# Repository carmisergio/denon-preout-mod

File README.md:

# Denon AVR-X1300W Pre-out mod

The scope of this project is adding line-level outputs to the Denon AVR-X1300W AV Receiver.
This can be acheived by getting the low-level signals from the digital board of the receiver before they make their way to the power amp board.

The "Vampire PCB" is soldered directly to the digital board of the receiverr, and provides an 8-pin JST PH connector with the signals. A small length of shielded cable brings them to the back panel of the unit, where removing the AM/FM tuner unit provides a convenient place to mount a miniature circular connector.

An external "Gain Box" amplifies the ~150Vrms internal signal to a usable (variable) line level with a single stage of op-amp amplification. It also processes the 12V signal coming from the receiver to operate muting relays on the output and generate a standard 12V trigger signal which can be used to control the amplifiers.

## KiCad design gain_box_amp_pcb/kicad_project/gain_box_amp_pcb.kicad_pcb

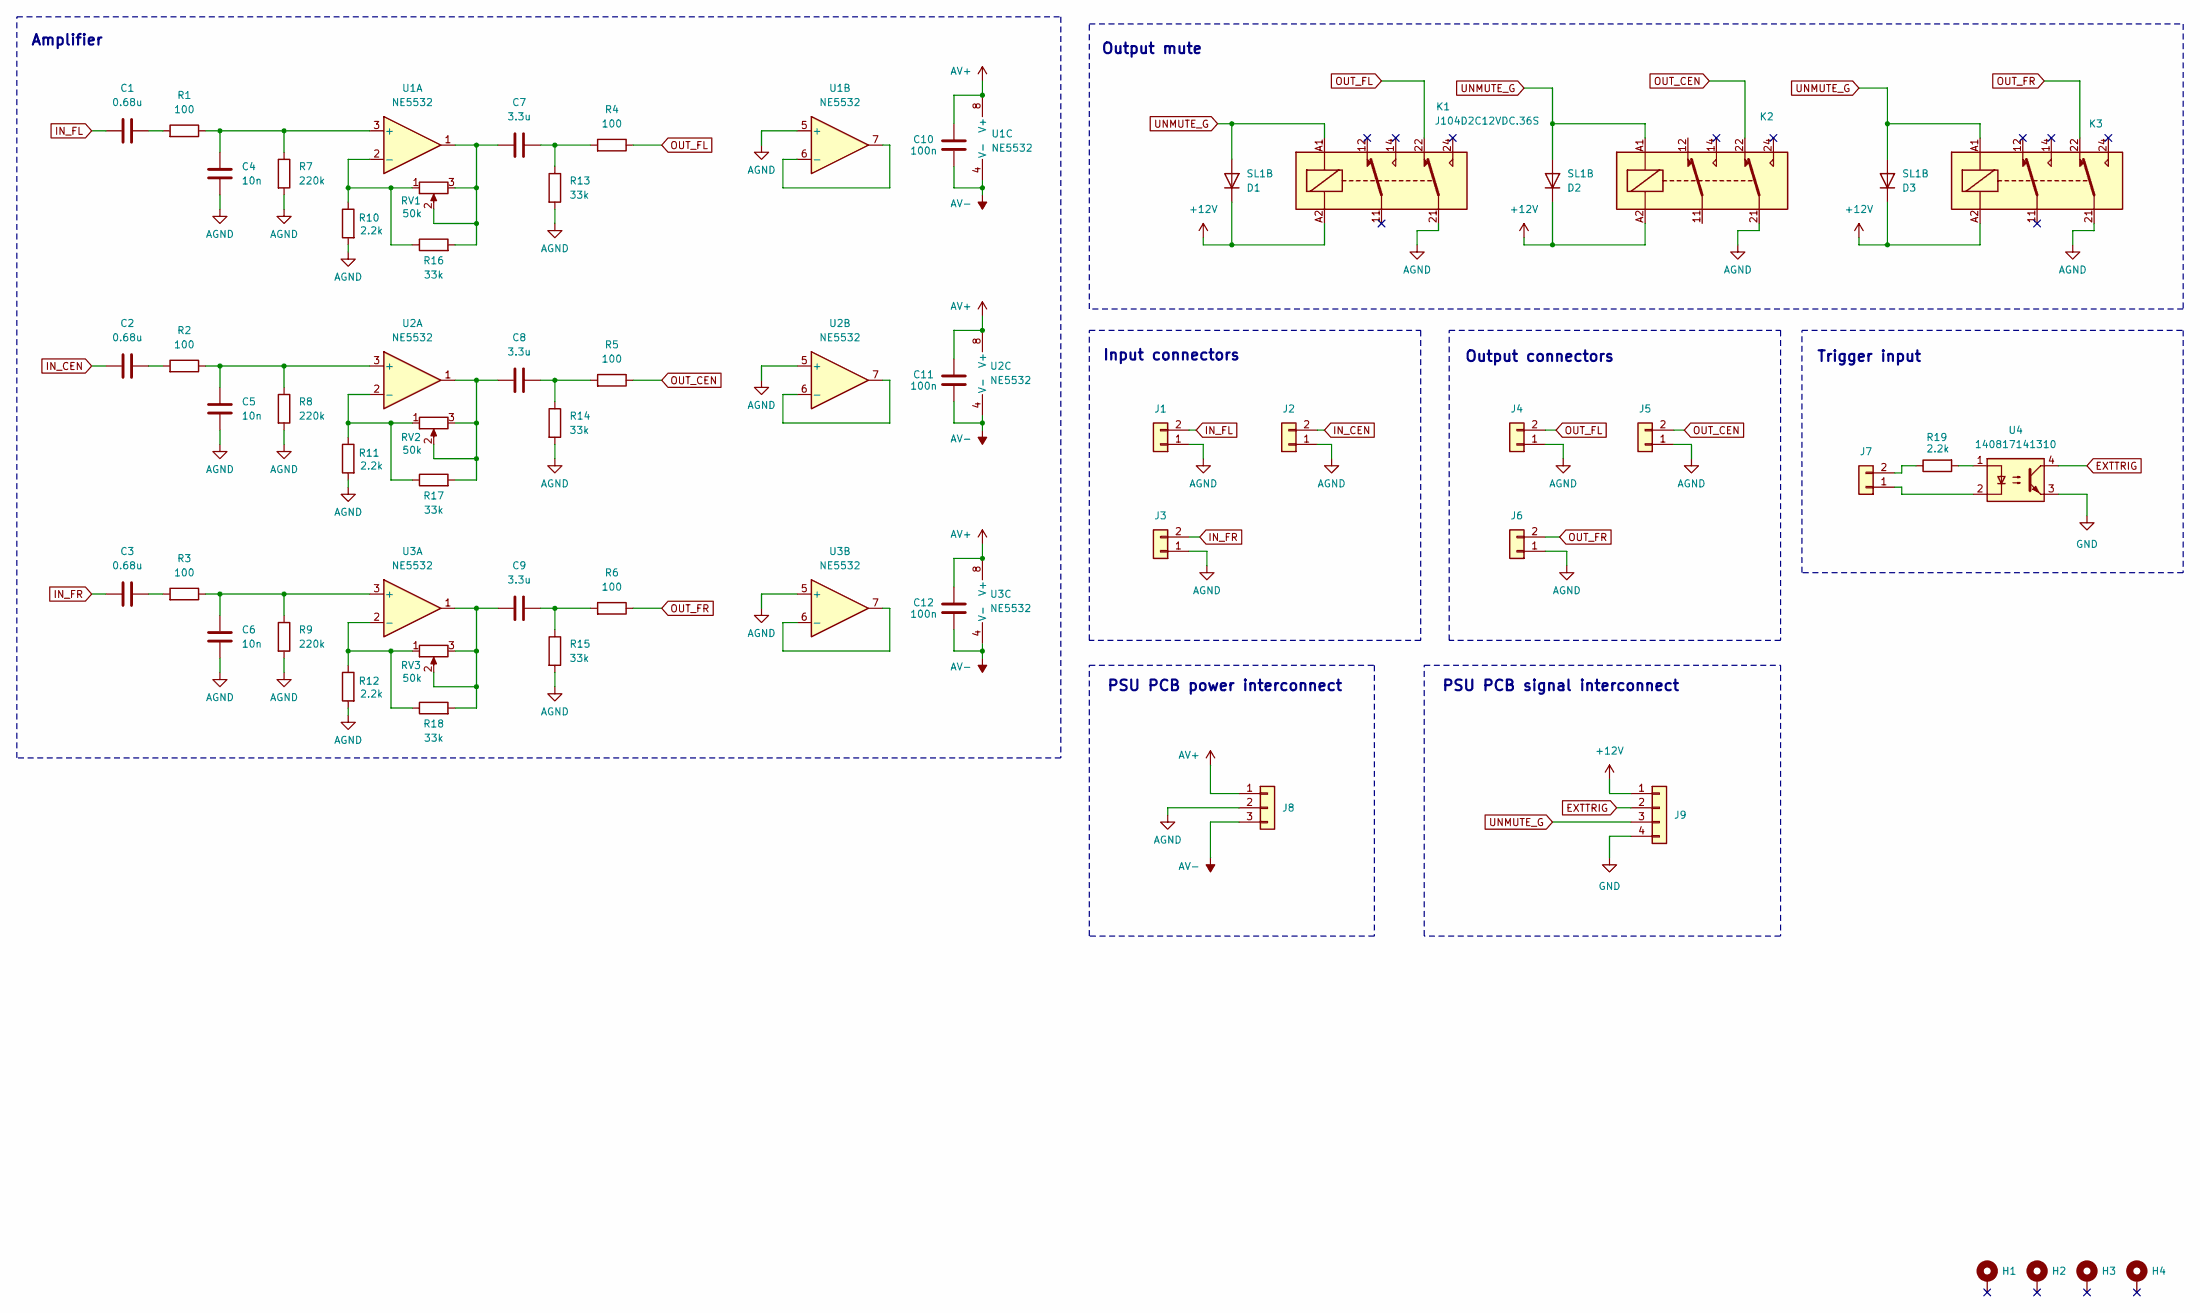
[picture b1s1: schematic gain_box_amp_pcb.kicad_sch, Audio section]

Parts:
C1, C2, C3: 0.68u; C_Rect_L18.0mm_W11.0mm_P15.00mm_FKS3_FKP3
C4, C5, C6: 10n; C_Rect_L13.0mm_W5.0mm_P10.00mm_FKS3_FKP3_MKS4
C7, C8, C9: 3.3u; C_Rect_L31.5mm_W12.5mm_P27.50mm_MKS4
C10, C11, C12: 100n; C_Disc_D3.8mm_W2.6mm_P2.50mm
D1, D2, D3: SL1B; D_SOD-123
H1, H2, H3, H4: MountingHole_Pad; MountingHole_3.2mm_M3_Pad_Via
J1, J2, J3, J4, J5, J6, J7: Conn_01x02; JST_PH_B2B-PH-K_1x02_P2.00mm_Vertical
J8: Conn_01x03; JST_VH_B3P-VH-B_1x03_P3.96mm_Vertical
J9: Conn_01x04; JST_PH_B4B-PH-K_1x04_P2.00mm_Vertical
K1, K2, K3: J104D2C12VDC.36S; Relay_DPDT_Finder_30.22
R1, R2, R3, R4, R5, R6: 100; R_Axial_DIN0207_L6.3mm_D2.5mm_P7.62mm_Horizontal
R7, R8, R9: 220k; R_Axial_DIN0207_L6.3mm_D2.5mm_P7.62mm_Horizontal
R10, R11, R12, R19: 2.2k; R_Axial_DIN0207_L6.3mm_D2.5mm_P7.62mm_Horizontal
R13, R14, R15, R16, R17, R18: 33k; R_Axial_DIN0207_L6.3mm_D2.5mm_P7.62mm_Horizontal
RV1, RV2, RV3: 50k; TRIM_PV36W503C01B00
U1, U2, U3: NE5532; DIP-8_W7.62mm
U4: 140817141310; DIP-4_W7.62mm

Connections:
+12V: D1.1 (K), D2.1 (K), D3.1 (K), J9.1, K1.A2, K2.A2, K3.A2
AGND: C4.1, C5.1, C6.1, J1.1, J2.1, J3.1, J4.1, J5.1, J6.1, J8.2, K1.21, K2.21, K3.21, R7.2, R8.2, R9.2, R10.2, R11.2, R12.2, R13.2, R14.2, R15.2, U1.5 (+), U2.5 (+), U3.5 (+)
AV+: C10.2, C11.2, C12.2, J8.1, U1.8 (V+), U2.8 (V+), U3.8 (V+)
AV-: C10.1, C11.1, C12.1, J8.3, U1.4 (V-), U2.4 (V-), U3.4 (V-)
EXTTRIG: J9.2, U4.4
GND: J9.4, U4.3
IN_CEN: C2.1, J2.2
IN_FL: C1.1, J1.2
IN_FR: C3.1, J3.2
unnamed: C1.2, R1.2
unnamed: C2.2, R2.2
unnamed: C3.2, R3.2
unnamed: C7.1, R16.2, RV1.2, RV1.3, U1.1
unnamed: C7.2, R4.2, R13.1
unnamed: C8.1, R17.2, RV2.2, RV2.3, U2.1
unnamed: C8.2, R5.2, R14.1
unnamed: C9.1, R18.2, RV3.2, RV3.3, U3.1
unnamed: C9.2, R6.2, R15.1
unnamed: J7.1, U4.2
unnamed: J7.2, R19.1
unnamed: R19.2, U4.1
unnamed: C4.2, R1.1, R7.1, U1.3 (+)
unnamed: R10.1, R16.1, RV1.1, U1.2 (-)
unnamed: U1.6 (-), U1.7
unnamed: C5.2, R2.1, R8.1, U2.3 (+)
unnamed: R11.1, R17.1, RV2.1, U2.2 (-)
unnamed: U2.6 (-), U2.7
unnamed: C6.2, R3.1, R9.1, U3.3 (+)
unnamed: R12.1, R18.1, RV3.1, U3.2 (-)
unnamed: U3.6 (-), U3.7
OUT_CEN: J5.2, K2.22, R5.1
OUT_FL: J4.2, K1.22, R4.1
OUT_FR: J6.2, K3.22, R6.1
UNMUTE_G: D1.2 (A), D2.2 (A), D3.2 (A), J9.3, K1.A1, K2.A1, K3.A1

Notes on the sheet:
PSU PCB signal interconnect
Output connectors
Amplifier
PSU PCB power interconnect
Trigger input
Output mute
Input connectors

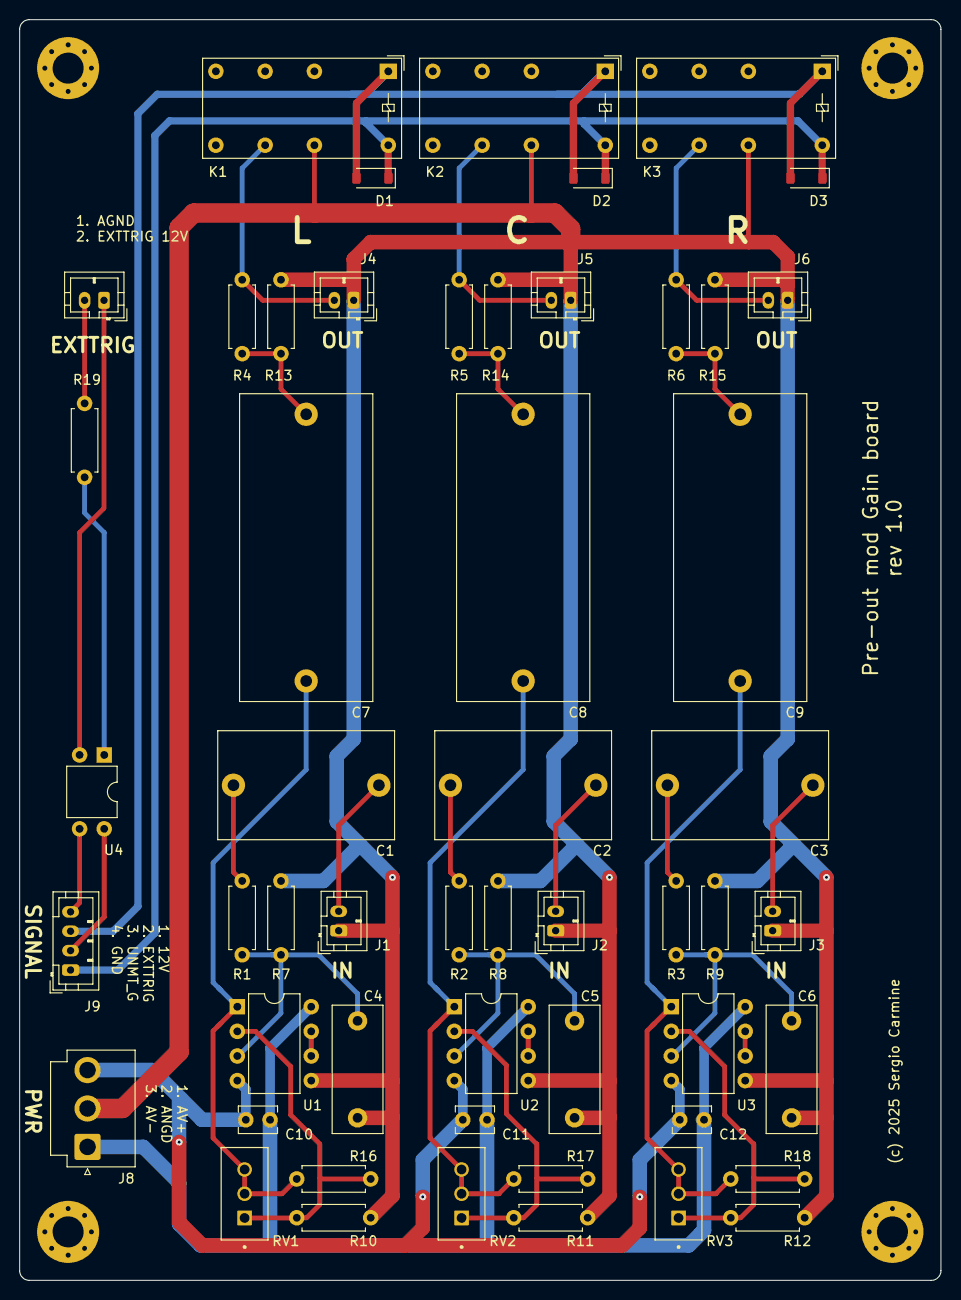
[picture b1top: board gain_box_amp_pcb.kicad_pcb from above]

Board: 2 copper layers, 95.0 x 130.0 mm, 57 parts (0 on the bottom side), 34 nets.

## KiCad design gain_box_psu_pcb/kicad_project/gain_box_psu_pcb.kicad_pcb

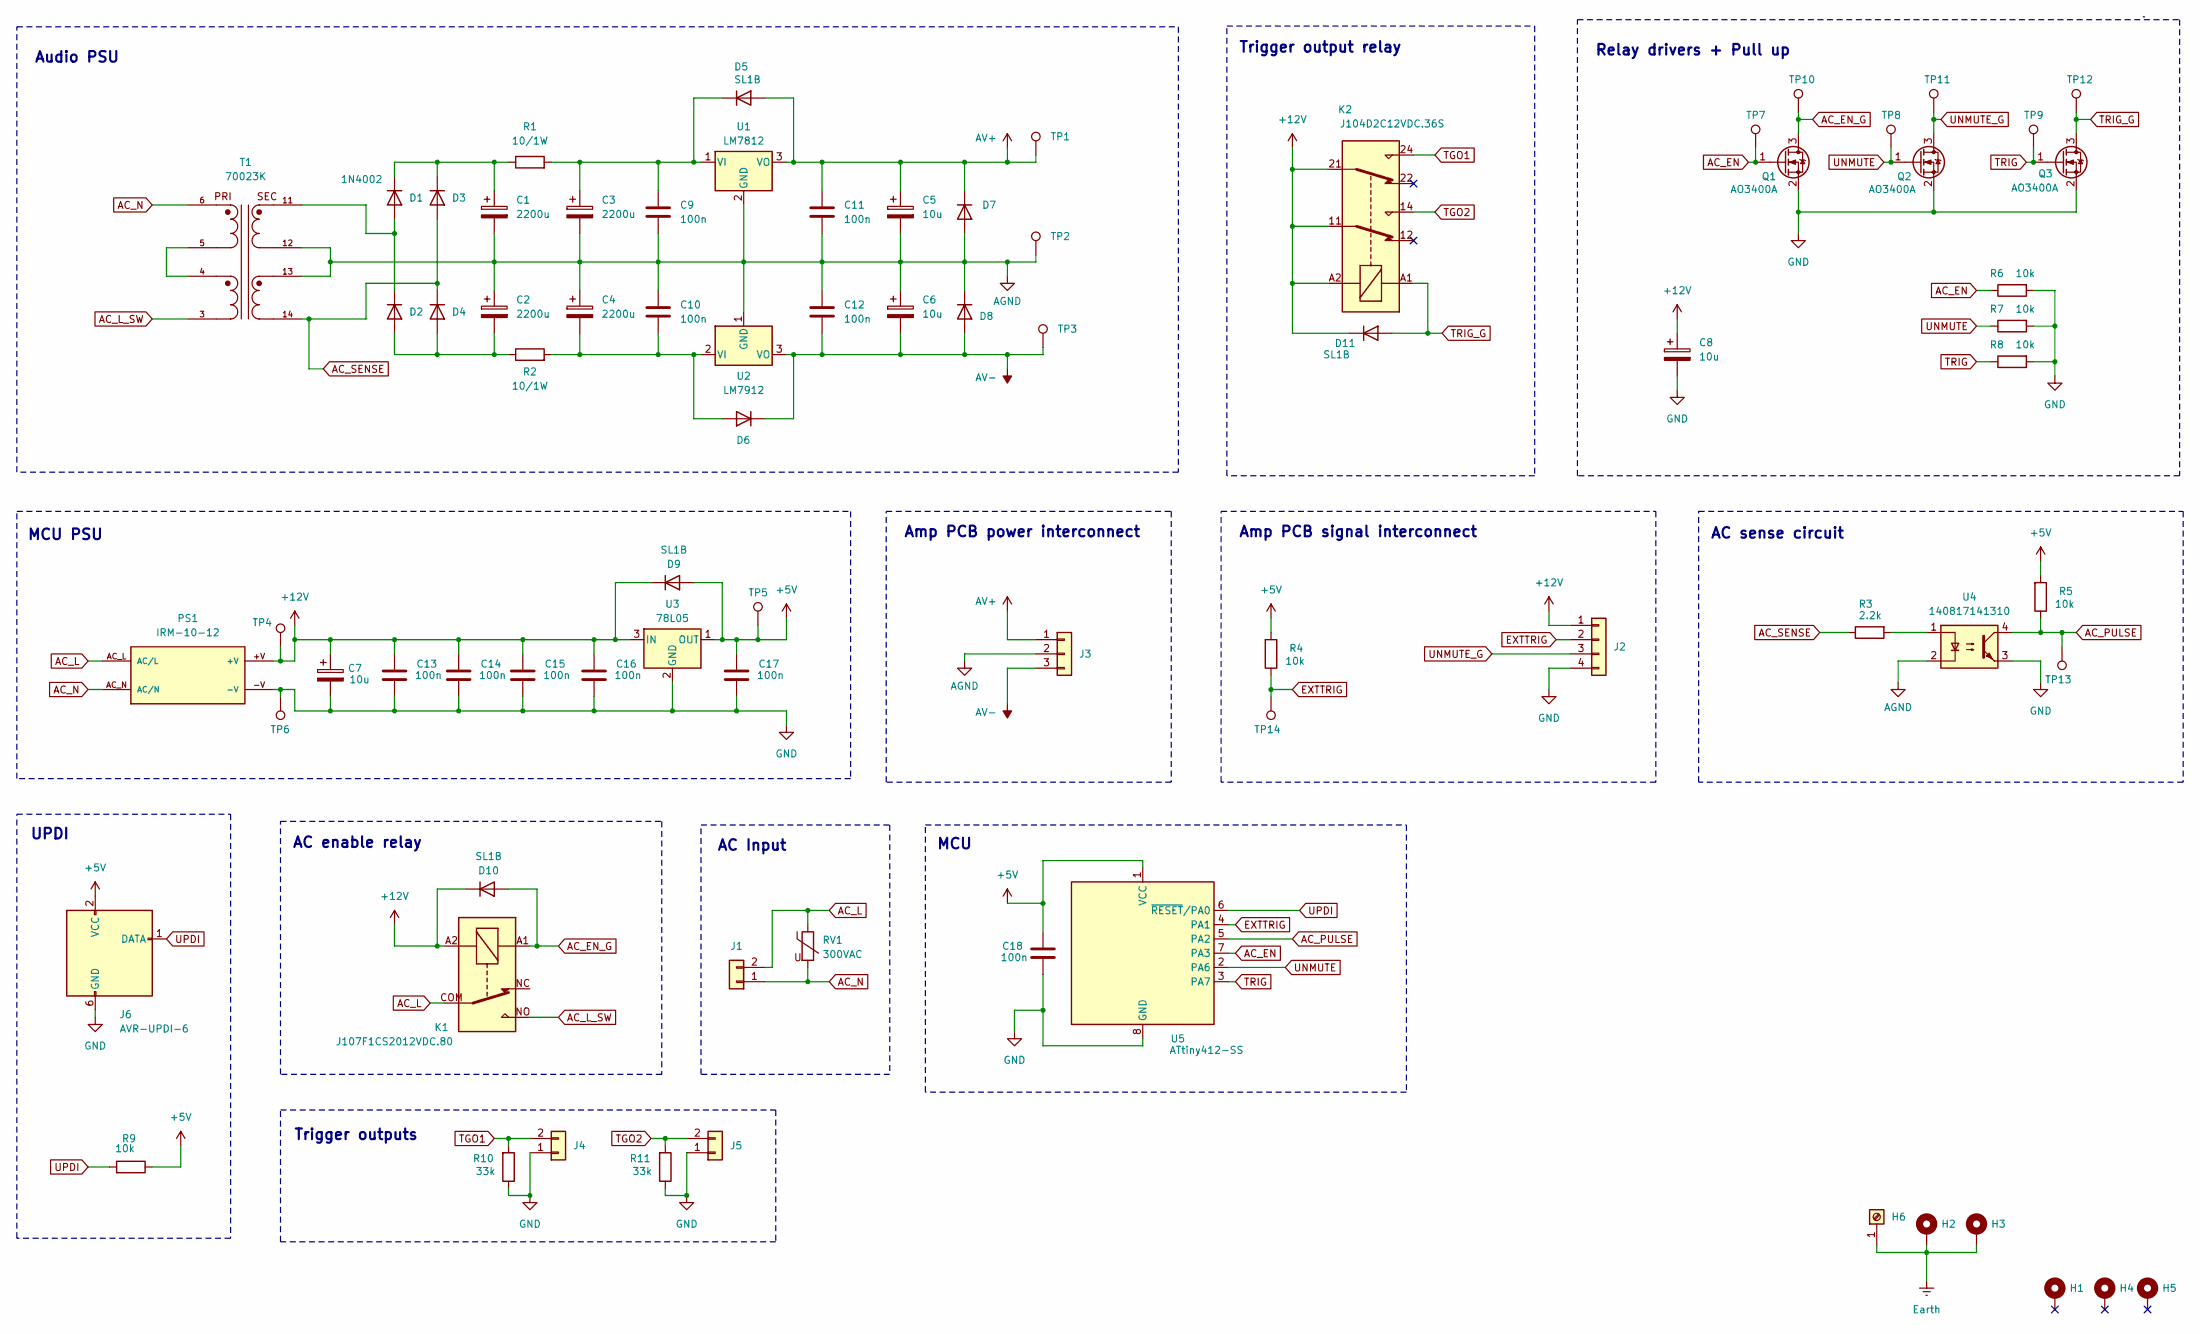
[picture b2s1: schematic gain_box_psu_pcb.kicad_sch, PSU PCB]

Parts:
C1, C2, C3, C4: 2200u; CP_Radial_D18.0mm_P7.50mm
C5, C6, C7, C8: 10u; CP_Radial_D5.0mm_P2.00mm
C9, C10, C11, C12, C13, C14, C15, C16, C17, C18: 100n; C_Disc_D3.8mm_W2.6mm_P2.50mm
D1, D2, D3, D4: 1N4002; D_DO-41_SOD81_P10.16mm_Horizontal
D5, D6, D7, D8, D9, D10, D11: SL1B; D_SOD-123
H1, H2, H3, H4, H5: MountingHole_Pad; MountingHole_3.2mm_M3_Pad_Via
H6: Screw_Terminal_01x01; KEYSTONE_7760
J1: Conn_01x02; JST_VH_B2P3-VH_1x02_P7.92mm_Vertical
J2: Conn_01x04; JST_PH_B4B-PH-K_1x04_P2.00mm_Vertical
J3: Conn_01x03; JST_VH_B3P-VH-B_1x03_P3.96mm_Vertical
J4, J5: Conn_01x02; JST_PH_B2B-PH-K_1x02_P2.00mm_Vertical
J6: AVR-UPDI-6; PinHeader_2x03_P2.54mm_Vertical
K1: J107F1CS2012VDC.80; RELAY_SRD-C
K2: J104D2C12VDC.36S; Relay_DPDT_Finder_30.22
PS1: IRM-10-12; CONV_IRM-10-12; PARTREV 2022-04-25
Q1, Q2, Q3: AO3400A; SOT-23
R1, R2: 10/1W; R_Axial_DIN0411_L9.9mm_D3.6mm_P12.70mm_Horizontal
R3: 2.2k; R_Axial_DIN0207_L6.3mm_D2.5mm_P7.62mm_Horizontal
R4, R5, R6, R7, R8, R9: 10k; R_0805_2012Metric_Pad1.20x1.40mm_HandSolder
R10, R11: 33k; R_Axial_DIN0207_L6.3mm_D2.5mm_P7.62mm_Horizontal
RV1: 300VAC; RV_Disc_D9mm_W4.5mm_P5mm
T1: 70023K; TRANS_Talema_70023K; PARTREV 11/20
TP1, TP2, TP3, TP4, TP5, TP6: TestPoint; TestPoint_Pad_D2.0mm
TP7, TP8, TP9, TP10, TP11, TP12, TP13, TP14: TestPoint; TestPoint_Pad_D1.0mm
U1: LM7812; TO-220-3_Vertical
U2: LM7912; TO-220-3_Vertical
U3: 78L05; SOT-89-3
U4: 140817141310; DIP-4_W7.62mm
U5: ATtiny412-SS; SOIC-8_3.9x4.9mm_P1.27mm

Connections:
+5V: C17.1, C18.1, D9.2 (A), J6.2 (VCC), R4.2, R5.2, R9.1, TP5.1, U3.1 (OUT), U5.1 (VCC)
+12V: C7.1, C8.1, C13.1, C14.1, C15.1, C16.1, D9.1 (K), D10.1 (K), D11.1 (K), J2.1, K1.A2, K2.11, K2.21, K2.A2, PS1.+V, TP4.1, U3.3 (IN)
AC_EN: Q1.1 (G), R6.1, TP7.1, U5.7 (PA3)
AC_EN_G: D10.2 (A), K1.A1, Q1.3 (D), TP10.1
AC_L: J1.2, K1.COM, PS1.AC_L (AC/L), RV1.1
AC_L_SW: K1.NO, T1.3
AC_N: J1.1, PS1.AC_N (AC/N), RV1.2, T1.6
AC_PULSE: R5.1, TP13.1, U4.4, U5.5 (PA2)
AC_SENSE: D3.2 (A), D4.1 (K), R3.1, T1.14
AGND: C1.2, C2.1, C3.2, C4.1, C5.2, C6.1, C9.2, C10.1, C11.2, C12.1, D7.2 (A), D8.1 (K), J3.2, T1.12, T1.13, TP2.1, U1.2 (GND), U2.1 (GND), U4.2
AV+: C5.1, C11.1, D5.2 (A), D7.1 (K), J3.1, TP1.1, U1.3 (VO)
AV-: C6.2, C12.2, D6.1 (K), D8.2 (A), J3.3, TP3.1, U2.3 (VO)
EXTTRIG: J2.2, R4.1, TP14.1, U5.4 (PA1)
Earth: H2.1, H3.1, H6.1
GND: C7.2, C8.2, C13.2, C14.2, C15.2, C16.2, C17.2, C18.2, J2.4, J4.1, J5.1, J6.6 (GND), PS1.-V, Q1.2 (S), Q2.2 (S), Q3.2 (S), R6.2, R7.2, R8.2, R10.1, R11.1, TP6.1, U3.2 (GND), U4.3, U5.8 (GND)
unnamed: D1.2 (A), D2.1 (K), T1.11
unnamed: C1.1, D1.1 (K), D3.1 (K), R1.1
unnamed: C2.2, D2.2 (A), D4.2 (A), R2.1
unnamed: C3.1, C9.1, D5.1 (K), R1.2, U1.1 (VI)
unnamed: C4.2, C10.2, D6.2 (A), R2.2, U2.2 (VI)
unnamed: R3.2, U4.1
unnamed: T1.4, T1.5
TGO1: J4.2, K2.24, R10.2
TGO2: J5.2, K2.14, R11.2
TRIG: Q3.1 (G), R8.1, TP9.1, U5.3 (PA7)
TRIG_G: D11.2 (A), K2.A1, Q3.3 (D), TP12.1
UNMUTE: Q2.1 (G), R7.1, TP8.1, U5.2 (PA6)
UNMUTE_G: J2.3, Q2.3 (D), TP11.1
UPDI: J6.1 (DATA), R9.2, U5.6 (~RESET/PA0)

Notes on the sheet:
Amp PCB signal interconnect
Trigger output relay
Amp PCB power interconnect
AC sense circuit
Relay drivers + Pull up
Audio PSU
Trigger outputs
MCU PSU
AC Input
AC enable relay
UPDI
MCU

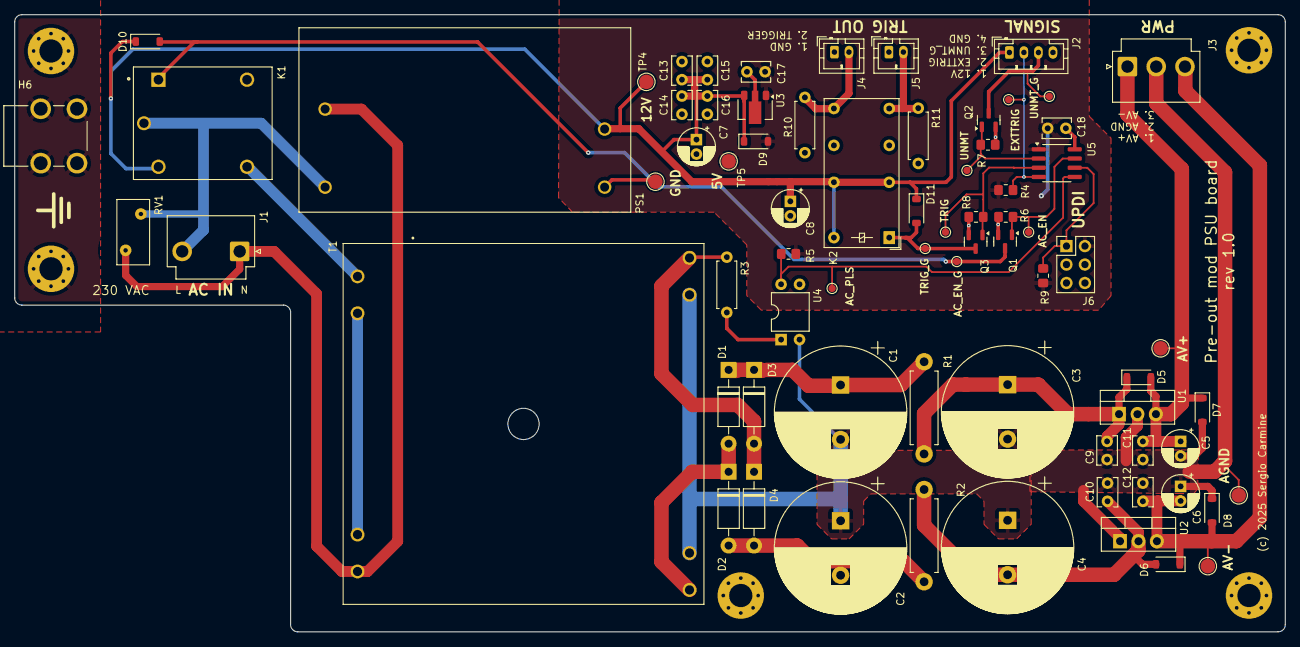
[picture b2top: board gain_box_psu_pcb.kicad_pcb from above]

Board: 2 copper layers, 175.0 x 85.0 mm, 79 parts (0 on the bottom side), 29 nets.

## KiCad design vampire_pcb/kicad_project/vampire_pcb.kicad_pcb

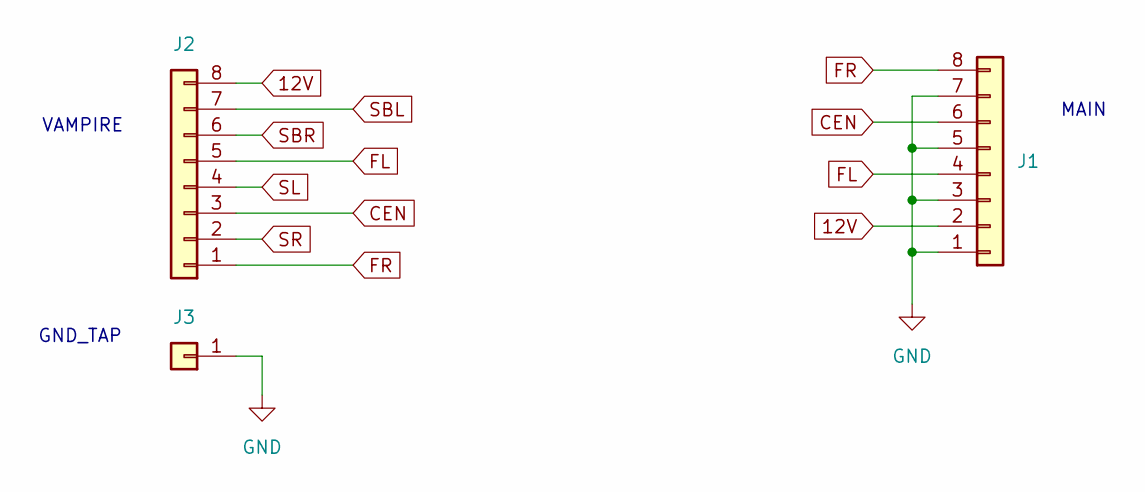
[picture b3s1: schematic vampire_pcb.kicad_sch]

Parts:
J1: Conn_01x08; JST_PH_B8B-PH-K_1x08_P2.00mm_Vertical
J2: VAMPIRE_EDGE; PinSocket_1x08_P2.54mm_Vertical
J3: GND_PAD; TestPoint_Pad_4.0x4.0mm

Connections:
12V: J1.2, J2.8
CEN: J1.6, J2.3
FL: J1.4, J2.5
FR: J1.8, J2.1
GND: J1.1, J1.3, J1.5, J1.7, J3.1
SBL: J2.7
SBR: J2.6
SL: J2.4
SR: J2.2

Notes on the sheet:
GND_TAP
MAIN
VAMPIRE

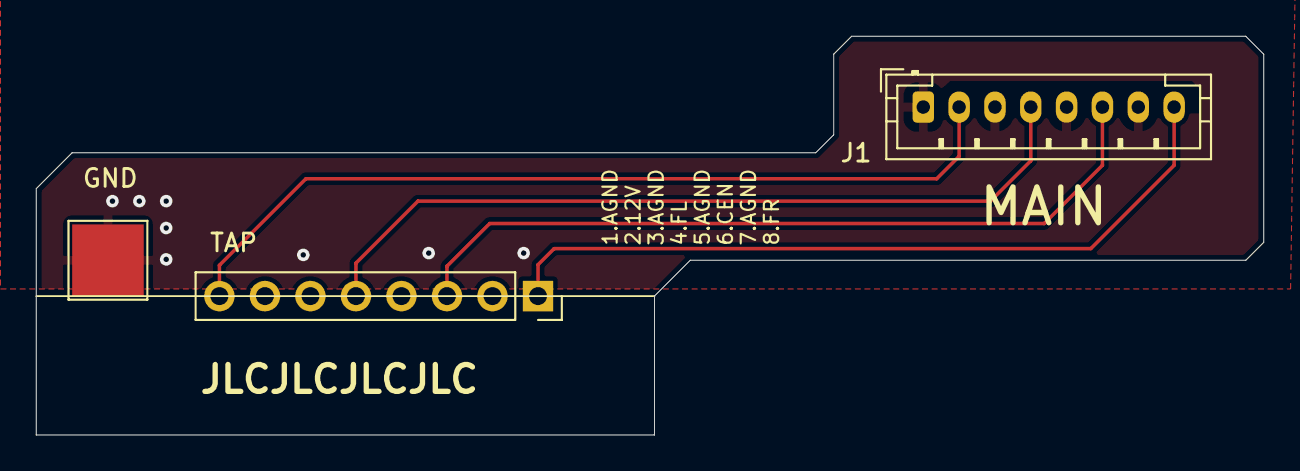
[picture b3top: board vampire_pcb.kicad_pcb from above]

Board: 2 copper layers, 68.5 x 22.2 mm, 3 parts (0 on the bottom side), 5 nets.

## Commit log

2024-04-10 vampire_pcb: first commit
2024-04-10 vampire_pcb: use copper pour for GND on front
2024-08-21 Update PCB
2024-09-19 Vampire PCB
2024-09-19 Gain box PCB + firmware
2024-09-21 firmware: implement millis for ATtiny412
2024-09-21 gain_box: preliminary amp section layout
2024-09-22 gain_box: first audio PSU layout
2024-09-23 gain_box new PSU position
2024-09-28 Split PSU PCB
2024-09-28 Layout AMP PCB
2024-12-26 Shorten PSU PCB
2024-12-27 Update PSU PCB
2024-12-27 Fix routing error
2024-12-29 Route new amp board
2024-12-30 New main PSU caps
2025-01-02 Sent to production
2025-01-17 Fix firmware bug

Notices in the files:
gain_box_amp_pcb/kicad_project/gain_box_amp_pcb.kicad_pcb:
(c) 2025 Sergio Carmine
